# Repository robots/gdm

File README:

Geodimeter toolkit

!!! WARNING !!!

All tools in this repository are "as is". No warranty at all. You break your station you pay for repair.

This project started as curiosity why can't I turn on this cheap 5500 station that i bought on internet. Lead to spending 4-5 months disassembling multiple firmwares from multiple stations. This all is work in progress, still evolving, still improving.

Tools available now:

docu - contains various documentation for Geodimeter totalstations 400/500/4000/600
gdm600 - tools for geodimeter 600
gdm-iface - interface to communicate with 400/500/4000 series of stations

If you find problem, or have some more information, or have fix for some tool use github's issue tracking system.

If you like the work here we are doing, consider sponsoring this project :-) Thank you.

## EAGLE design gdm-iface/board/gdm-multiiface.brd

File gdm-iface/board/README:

WIP project of multi interface board. This board contains:

connector for 400/500/4000 stations
external serial connector
level translators 3v to 5v
dcdc converter for powering mcu
radio
max232
stm32 bluepill
-12V dc dc (optional, for angular board interfacing)

Aim of this board is:

- interface for programming of 400/500/4000 stations with serial communication - this is working!
- radio interface for gdm600 station - not implemented in firmware
- radio interface for computer - counterpart to upper radio - not implemented
- direct interface to gdm boards - angle/servo - needs firmware modification
- 4x servo output - used for 400station calibration - working, needs better software for calibration calculation.

Notes on build:

-when mounting dc dc converter board be sure to use diode as one "leg" (on output "+" signal). This will prevent 5v going from usb to dcdc converter
-be sure to use genuine STM32 bluepill - some bluepills use different mcu that contains different USB peripheral - not working with our firmware.
-set dc dc to 5.0volts (+diode forward voltage) before plugging in bluepill and level translators. This will prevent from frying them.

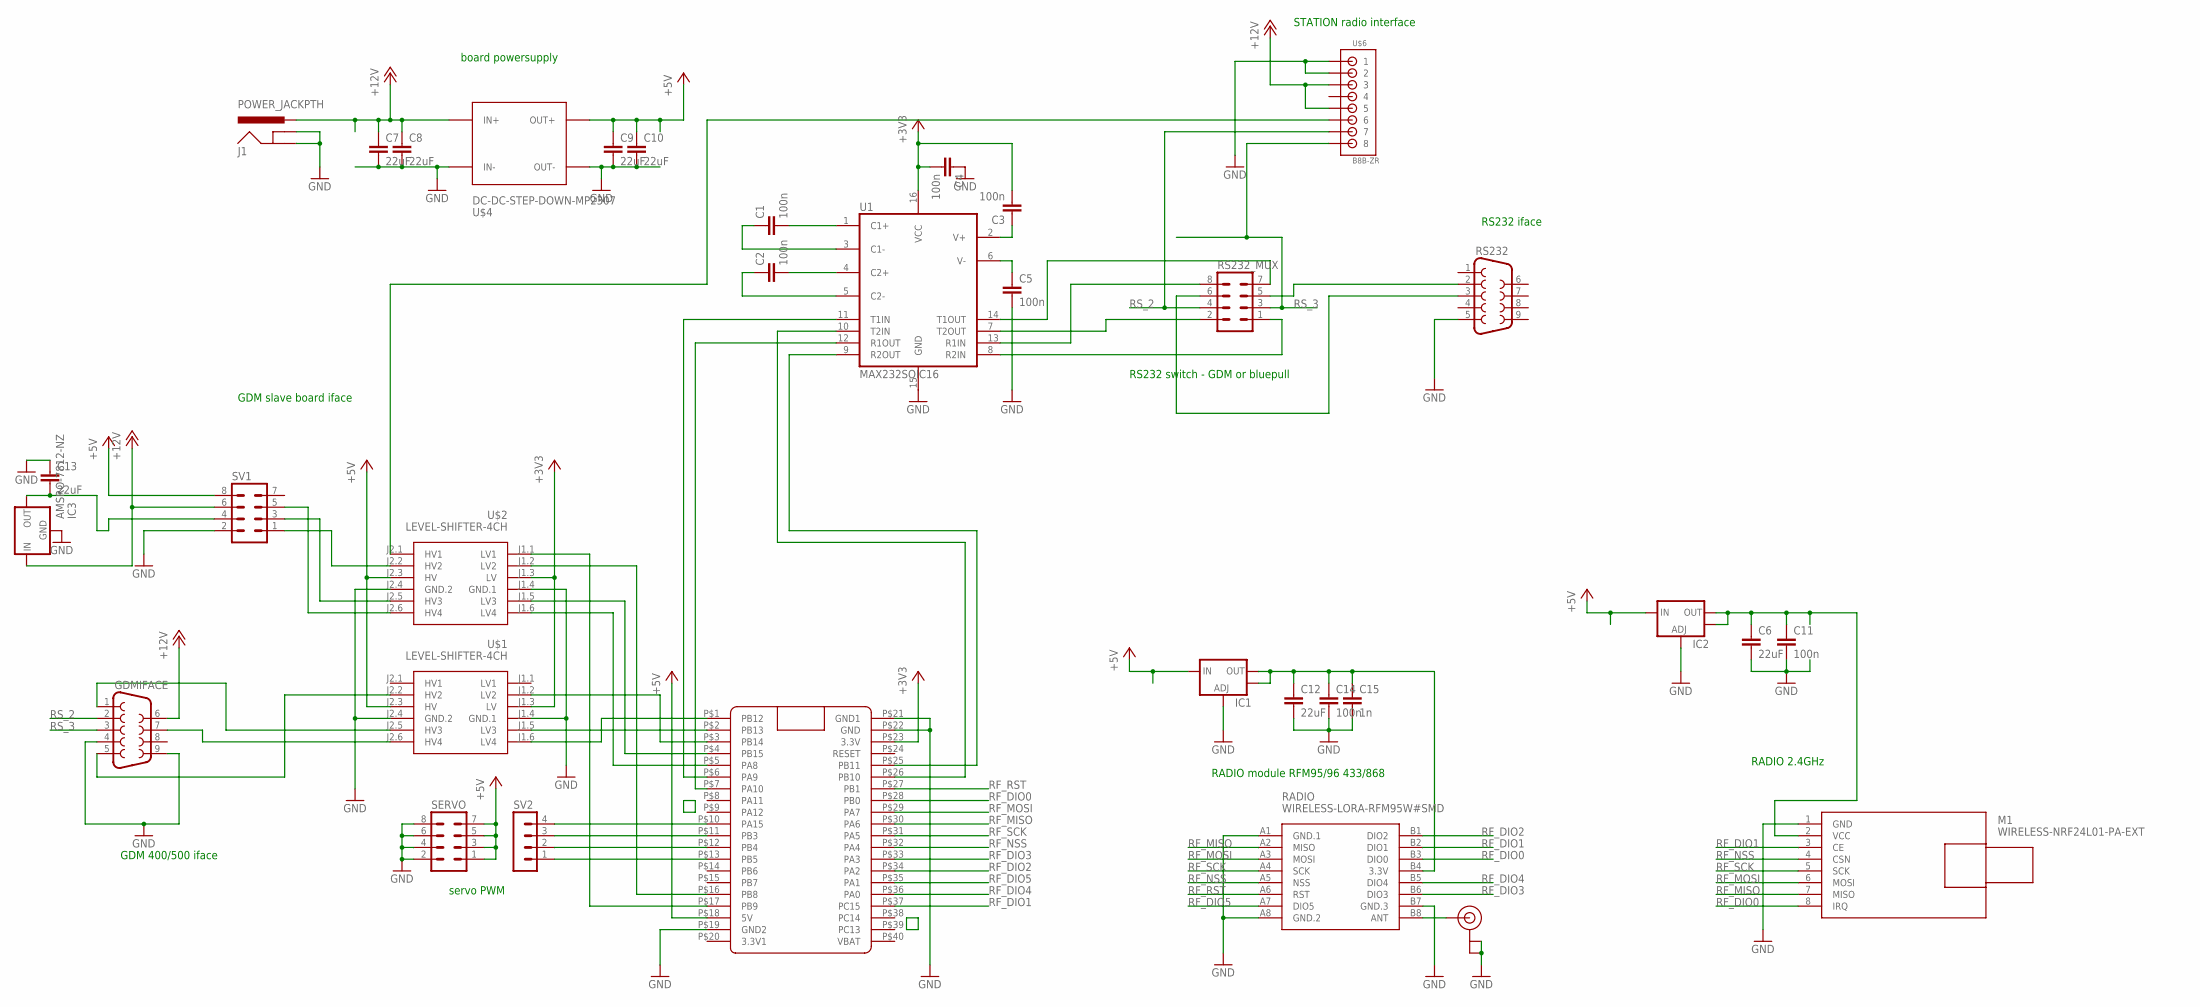
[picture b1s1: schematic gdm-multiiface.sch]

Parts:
BLUEPILL: BLUE_PILL
C1, C2, C3, C4, C5: 100n; C0805
C6, C7, C8, C9, C10, C12, C13: 22uF; C1210K
C11, C14: 100n; C0805K
C15: 1n; C0805K
GDMIFACE: DB9FEMALE; DB9
IC1, IC2: V_REG_LM1117SOT223; SOT223
IC3: AMSRO-7812-NZ; 79XXS
J1: POWER_JACKPTH; POWER_JACK_PTH
M1: WIRELESS-NRF24L01-PA-EXT
RADIO: WIRELESS-LORA-RFM95W#SMD
RS232: DB9FEMALE; DB9
RS232_MUX: MA04-2
SERVO: MA04-2
SV1: MA04-2
SV2: MA04-1
U1: MAX232SOIC16; SO016
U$1, U$2: LEVEL-SHIFTER-4CH
U$3: U.FL
U$4: DC-DC-STEP-DOWN-MP2307
U$6: B8B-ZR

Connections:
+3V3: BLUEPILL.P$23 (3.3V), C3.2, C4.2, U1.16 (VCC), U$1.J1.3 (LV), U$2.J1.3 (LV)
+5V: BLUEPILL.P$18 (5V), C9.1, C10.1, IC1.3 (IN), IC2.3 (IN), SERVO.1, SERVO.3, SERVO.5, SERVO.7, SV1.8, U$1.J2.3 (HV), U$2.J2.3 (HV), U$4.OUT+
+12V: C7.1, C8.1, GDMIFACE.6, IC3.IN, J1.PWR, SV1.6, U$4.IN+, U$6.3, U$6.5
-12V: C13.2, IC3.OUT, SV1.4
GND: BLUEPILL.P$19 (GND2), BLUEPILL.P$21 (GND1), BLUEPILL.P$22 (GND), C4.1, C5.2, C6.2, C7.2, C8.2, C9.2, C10.2, C11.2, C12.2, C13.1, C14.2, C15.2, GDMIFACE.4, GDMIFACE.9, IC1.1 (ADJ), IC2.1 (ADJ), IC3.GND, J1.GND, J1.GNDBREAK, M1.1 (GND), RADIO.A1 (GND.1), RADIO.A8 (GND.2), RADIO.B7 (GND.3), RS232.5, SERVO.2, SERVO.4, SERVO.6, SERVO.8, SV1.2, U1.15 (GND), U$1.J1.4 (GND.1), U$1.J2.4 (GND.2), U$2.J1.4 (GND.1), U$2.J2.4 (GND.2), U$3.P$1 (GND), U$3.P$2 (GND), U$4.IN-, U$4.OUT-, U$6.1, U$6.2
unnamed: RADIO.B8 (ANT), U$3.P$3 (SIGNAL)
unnamed: RS232_MUX.7, U1.14 (T1OUT)
unnamed: RS232_MUX.8, U1.13 (R1IN)
unnamed: C6.1, C11.1, IC2.2 (OUT), IC2.4 (OUT), M1.2 (VCC)
unnamed: BLUEPILL.P$10 (PA15), SV2.4
unnamed: C5.1, U1.6 (V-)
unnamed: C3.1, U1.2 (V+)
unnamed: BLUEPILL.P$11 (PB3), SV2.3
unnamed: BLUEPILL.P$6 (PA9), U1.11 (T1IN)
unnamed: BLUEPILL.P$7 (PA10), U1.12 (R1OUT)
unnamed: BLUEPILL.P$12 (PB4), SV2.2
unnamed: BLUEPILL.P$13 (PB5), SV2.1
unnamed: C12.1, C14.1, C15.1, IC1.2 (OUT), IC1.4 (OUT), RADIO.B4 (3.3V)
unnamed: RS232.2, RS232_MUX.5
unnamed: C1.2, U1.1 (C1+)
unnamed: C1.1, U1.3 (C1-)
unnamed: C2.2, U1.4 (C2+)
unnamed: C2.1, U1.5 (C2-)
unnamed: SV1.1, U$2.J2.2 (HV2)
unnamed: BLUEPILL.P$17 (PB9), U$2.J1.1 (LV1)
unnamed: BLUEPILL.P$4 (PB15), U$2.J1.5 (LV3)
unnamed: BLUEPILL.P$3 (PB14), U$1.J1.2 (LV2)
unnamed: BLUEPILL.P$2 (PB13), U$1.J1.5 (LV3)
unnamed: BLUEPILL.P$1 (PB12), U$1.J1.6 (LV4)
unnamed: GDMIFACE.7, U$1.J2.6 (HV4)
unnamed: GDMIFACE.1, U$1.J2.5 (HV3)
unnamed: GDMIFACE.5, U$1.J2.2 (HV2)
unnamed: SV1.3, U$2.J2.5 (HV3)
unnamed: SV1.5, U$2.J2.6 (HV4)
unnamed: BLUEPILL.P$5 (PA8), U$2.J1.6 (LV4)
unnamed: BLUEPILL.P$26 (PB10), U1.10 (T2IN)
unnamed: BLUEPILL.P$25 (PB11), U1.9 (R2OUT)
unnamed: RS232_MUX.2, U1.7 (T2OUT)
unnamed: RS232_MUX.1, U1.8 (R2IN)
unnamed: U$2.J2.1 (HV1), U$6.6
unnamed: RS232.3, RS232_MUX.6
unnamed: BLUEPILL.P$16 (PB8), U$2.J1.2 (LV2)
RF_DIO0: BLUEPILL.P$28 (PB0), M1.8 (IRQ), RADIO.B3 (DIO0)
RF_DIO1: BLUEPILL.P$37 (PC15), M1.3 (CE), RADIO.B2 (DIO1)
RF_DIO2: BLUEPILL.P$34 (PA2), RADIO.B1 (DIO2)
RF_DIO3: BLUEPILL.P$33 (PA3), RADIO.B6 (DIO3)
RF_DIO4: BLUEPILL.P$36 (PA0), RADIO.B5 (DIO4)
RF_DIO5: BLUEPILL.P$35 (PA1), RADIO.A7 (DIO5)
RF_MISO: BLUEPILL.P$30 (PA6), M1.7 (MISO), RADIO.A2 (MISO)
RF_MOSI: BLUEPILL.P$29 (PA7), M1.6 (MOSI), RADIO.A3 (MOSI)
RF_NSS: BLUEPILL.P$32 (PA4), M1.4 (CSN), RADIO.A5 (NSS)
RF_RST: BLUEPILL.P$27 (PB1), RADIO.A6 (RST)
RF_SCK: BLUEPILL.P$31 (PA5), M1.5 (SCK), RADIO.A4 (SCK)
RS_2: GDMIFACE.2, RS232_MUX.4, U$6.7
RS_3: GDMIFACE.3, RS232_MUX.3, U$6.8

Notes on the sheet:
GDM 400/500 iface
GDM slave board iface
board powersupply
RADIO module RFM95/96 433/868
RS232 iface
RS232 switch - GDM or bluepull
servo PWM
STATION radio interface
RADIO 2.4GHz

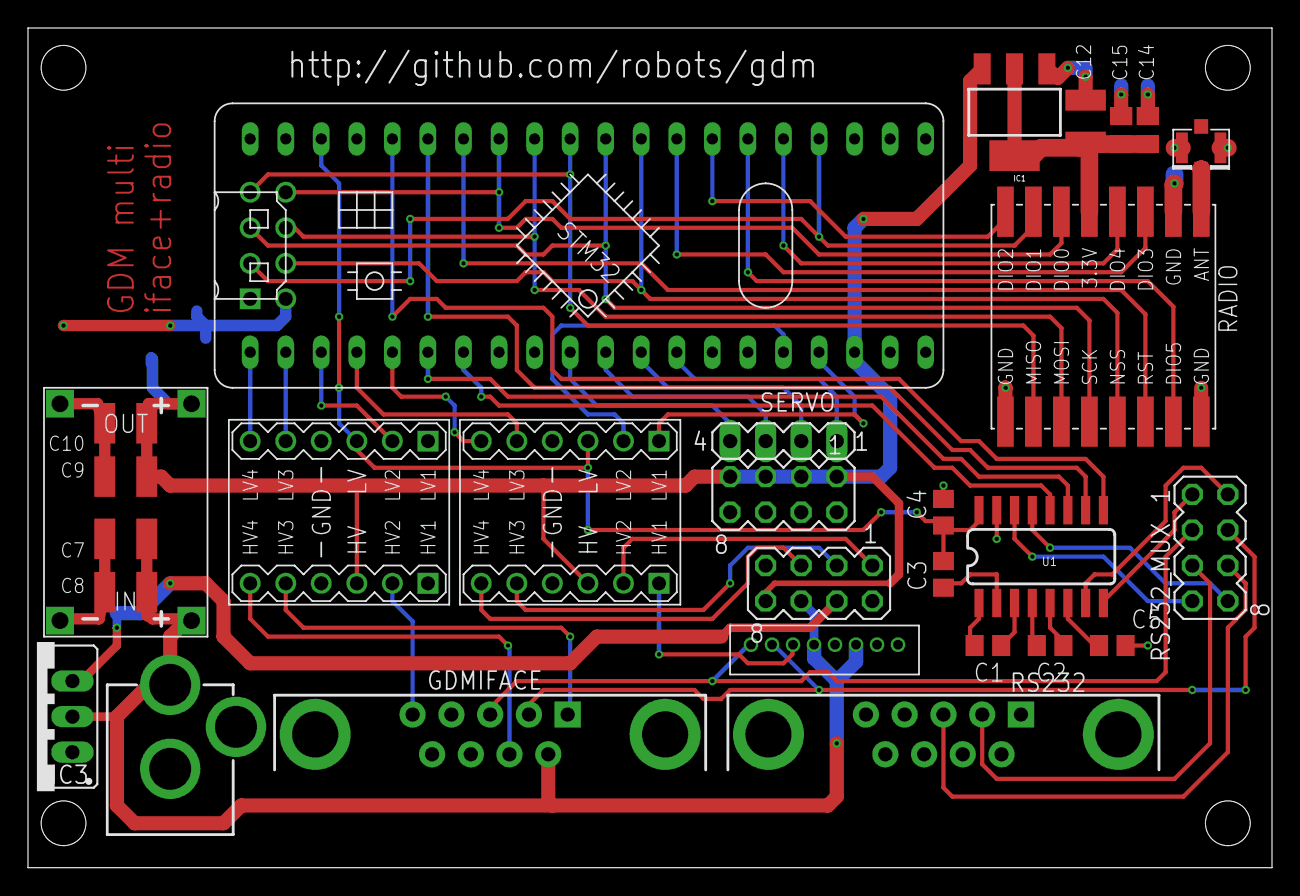
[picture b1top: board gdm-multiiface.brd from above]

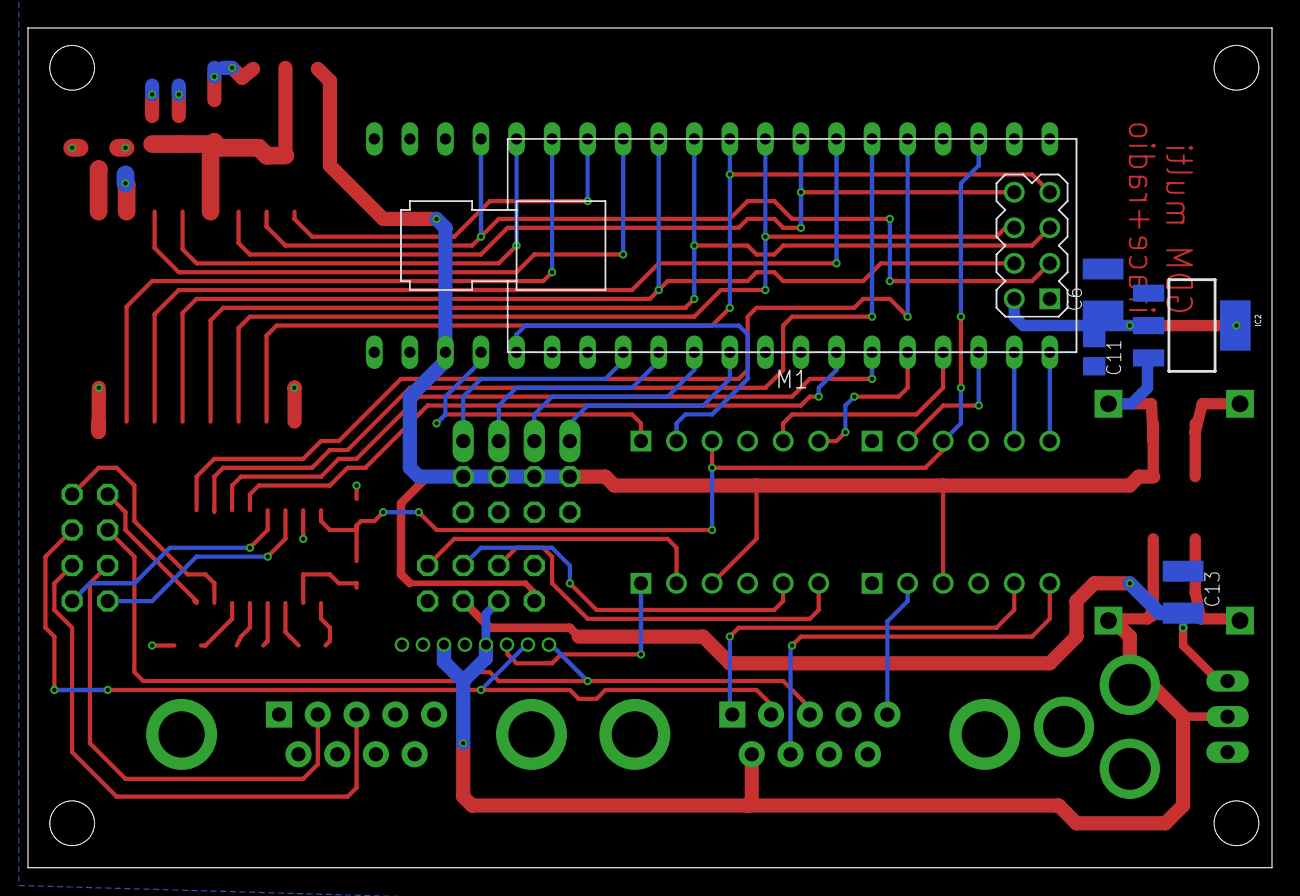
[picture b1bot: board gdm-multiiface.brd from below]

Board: 2 copper layers, 88.9 x 60.0 mm, 34 parts (5 on the bottom side), 55 nets.

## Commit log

2021-03-02 Initial commit - add docu,gdm-iface, gdm600 tools
2021-03-02 add README
2021-03-07 gdm600: update backuptool to latest working version.
2021-03-07 gdm600: first bank did not get saved, and all banks were off by one.
2021-03-07 gdm600: add tool to split fw.s to banks binaries
2021-03-07 gdm-iface-tool: add python dependency
2021-03-07 gdm600: fix srec2binarysplit.
    bank0 does not exist and remove debug output
2021-03-08 gdm600: fix uploading utility.
2021-03-08 Amend readme with dependencies.
2021-03-14 fix info in gdm600, add more documentation
2021-03-15 gdm600cu: new upload script to upload full memory dump back to CU
    tested only with ROM 648-02.00
2021-03-21 add 3d models to interface servos to servo-less station - for calibration
2021-04-09 gdm600: upload.py make output nicer.
2021-04-09 gdm600cu: better upload.py with ROM space skip
2021-04-09 doc: add documentation for used chips.
2021-04-09 gdm-iface-tool: change names of gdm4400 and 442 to 4000 and 400 respectively.
2021-04-09 gdm-iface-tool: fix recv command.
2021-05-10 gdm-iface: cleanup
2021-05-10 gdm-iface: add support for uart-bridge
    Board presents itself as 2 serial ports, first one is interface, second one is uart bridge. Uart bridge implements all baudrates (tested with 115200 and 9600) and odd/even parity, word size is 9 or 8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
2021-05-10 gdm-iface: add board schematic, layout and gerbers
2021-09-18 Add scanned documents.
2021-09-18 cleanup
2021-09-18 add support for gdm 220 family
2021-09-18 fw: fix padding
2022-02-19 gdm600cu: dump parser from text to bin.
2022-02-23 Add readme about interface board.
2022-02-23 add missing linker script.
2022-02-23 Change VID/PID and add driver for windows32.
2022-02-23 Add binary file and add description into readme.
2022-03-11 clean mess.
2022-03-11 add working uart1 driver.
2022-03-11 Add serial-port sniffer firmware for bluepill.
2022-03-20 some tool fixed in backup
2022-03-20 ifacetool: fix BCD decoding hopefuly forever.
2023-12-21 gdm-iface: update to multi interface configuration.
2023-12-21 gdm-iface-tool update to multiple interfaces.
2023-12-21 some small changes not commited in a long time.
2023-12-21 update openocd config.
2023-12-21 add more documentation
2023-12-21 example tool to talk to angle board.
2023-12-21 add spi to firmware
2025-01-26 Add Arduino version of gdm-iface
2025-01-26 Add more RAM dump information
2025-01-27 Add 608S teardown, documentation

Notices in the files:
parts and their libraries:
SparkFun: Licensing: CC v3.0 Share-Alike You are welcome to use this library for commercial purposes.
diy-modules: Released under the Creative Commons Attribution 4.0 International License: http://creativecommons.org/licenses/by/4.0
